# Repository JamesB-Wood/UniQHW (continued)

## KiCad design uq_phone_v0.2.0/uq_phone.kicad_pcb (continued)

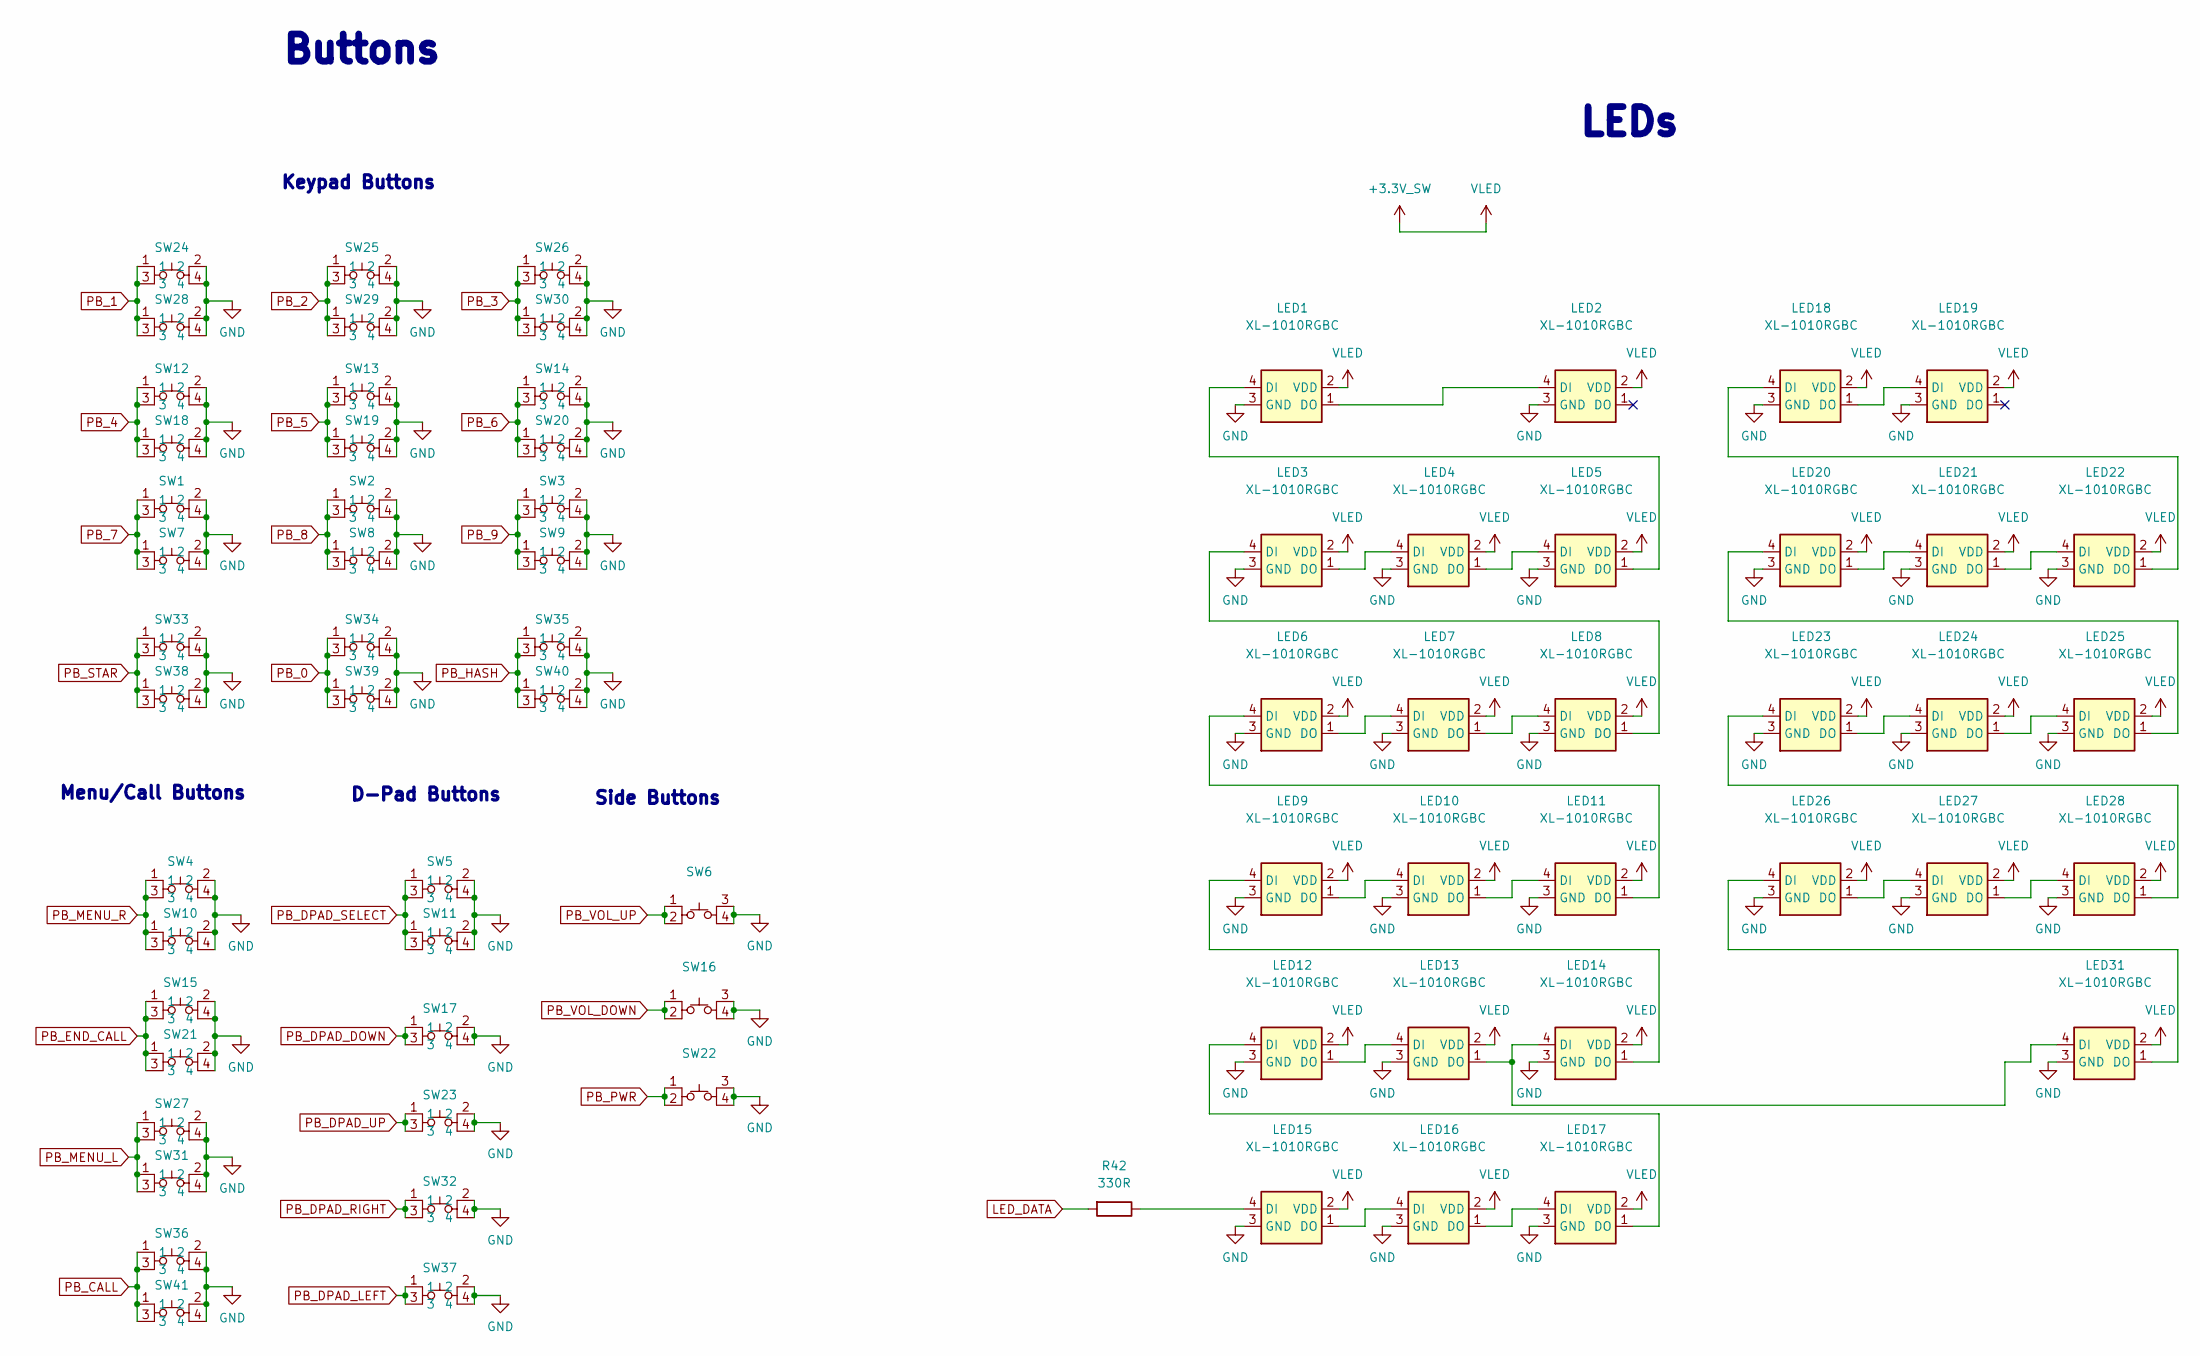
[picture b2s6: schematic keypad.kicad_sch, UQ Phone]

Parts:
LED1, LED2, LED3, LED4, LED5, LED6, LED7, LED8, LED9, LED10, LED11, LED12, LED13, LED14, LED15, LED16, LED17, LED18, LED20, LED21, LED22, LED23, LED24, LED25, LED26, LED27, LED28, LED31: XL-1010RGBC; XL-1010RGBC-WS2812B; LCSC PN C5349953
LED19: XL-1010RGBC; XL-1010RGBC-Alt; LCSC PN C5349953
R42: 330R; R_0402_1005Metric; LCSC PN C6117577
SW1, SW2, SW3, SW4, SW5, SW7, SW8, SW9, SW10, SW11, SW12, SW13, SW14, SW15, SW17, SW18, SW19, SW20, SW21, SW23, SW24, SW25, SW26, SW27, SW28, SW29, SW30, SW31, SW32, SW33, SW34, SW35, SW36, SW37, SW38, SW39, SW40, SW41: SKTAAAE010; LCSC PN C358616
SW6, SW16, SW22: SKSCLCE010; LCSC PN C139799

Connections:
+3.3V_SW: LED1.2 (VDD), LED2.2 (VDD), LED3.2 (VDD), LED4.2 (VDD), LED5.2 (VDD), LED6.2 (VDD), LED7.2 (VDD), LED8.2 (VDD), LED9.2 (VDD), LED10.2 (VDD), LED11.2 (VDD), LED12.2 (VDD), LED13.2 (VDD), LED14.2 (VDD), LED15.2 (VDD), LED16.2 (VDD), LED17.2 (VDD), LED18.2 (VDD), LED19.2 (VDD), LED20.2 (VDD), LED21.2 (VDD), LED22.2 (VDD), LED23.2 (VDD), LED24.2 (VDD), LED25.2 (VDD), LED26.2 (VDD), LED27.2 (VDD), LED28.2 (VDD), LED31.2 (VDD); also elsewhere on the board
GND: LED1.3 (GND), LED2.3 (GND), LED3.3 (GND), LED4.3 (GND), LED5.3 (GND), LED6.3 (GND), LED7.3 (GND), LED8.3 (GND), LED9.3 (GND), LED10.3 (GND), LED11.3 (GND), LED12.3 (GND), LED13.3 (GND), LED14.3 (GND), LED15.3 (GND), LED16.3 (GND), LED17.3 (GND), LED18.3 (GND), LED19.3 (GND), LED20.3 (GND), LED21.3 (GND), LED22.3 (GND), LED23.3 (GND), LED24.3 (GND), LED25.3 (GND), LED26.3 (GND), LED27.3 (GND), LED28.3 (GND), LED31.3 (GND), SW1.2, SW1.4, SW2.2, SW2.4, SW3.2, SW3.4, SW4.2, SW4.4, SW5.2, SW5.4, SW6.3, SW6.4, SW7.2, SW7.4, SW8.2, SW8.4, SW9.2, SW9.4, SW10.2, SW10.4, SW11.2, SW11.4, SW12.2, SW12.4, SW13.2, SW13.4, SW14.2, SW14.4, SW15.2, SW15.4, SW16.3, SW16.4, SW17.2, SW17.4, SW18.2, SW18.4, SW19.2, SW19.4, SW20.2, SW20.4, SW21.2, SW21.4, SW22.3, SW22.4, SW23.2, SW23.4, SW24.2, SW24.4, SW25.2, SW25.4, SW26.2, SW26.4, SW27.2, SW27.4, SW28.2, SW28.4, SW29.2, SW29.4, SW30.2, SW30.4, SW31.2, SW31.4, SW32.2, SW32.4, SW33.2, SW33.4, SW34.2, SW34.4, SW35.2, SW35.4, SW36.2, SW36.4, SW37.2, SW37.4, SW38.2, SW38.4, SW39.2, SW39.4, SW40.2, SW40.4, SW41.2, SW41.4; also elsewhere on the board
LED_DATA: R42.2; also elsewhere on the board
unnamed: LED1.4 (DI), LED5.1 (DO)
unnamed: LED1.1 (DO), LED2.4 (DI)
unnamed: LED3.4 (DI), LED8.1 (DO)
unnamed: LED3.1 (DO), LED4.4 (DI)
unnamed: LED4.1 (DO), LED5.4 (DI)
unnamed: LED6.1 (DO), LED7.4 (DI)
unnamed: LED7.1 (DO), LED8.4 (DI)
unnamed: LED9.1 (DO), LED10.4 (DI)
unnamed: LED10.1 (DO), LED11.4 (DI)
unnamed: LED6.4 (DI), LED11.1 (DO)
unnamed: LED12.4 (DI), LED17.1 (DO)
unnamed: LED12.1 (DO), LED13.4 (DI)
unnamed: LED13.1 (DO), LED14.4 (DI), LED31.4 (DI)
unnamed: LED9.4 (DI), LED14.1 (DO)
unnamed: LED15.4 (DI), R42.1
unnamed: LED15.1 (DO), LED16.4 (DI)
unnamed: LED16.1 (DO), LED17.4 (DI)
unnamed: LED18.4 (DI), LED22.1 (DO)
unnamed: LED18.1 (DO), LED19.4 (DI)
unnamed: LED20.4 (DI), LED25.1 (DO)
unnamed: LED20.1 (DO), LED21.4 (DI)
unnamed: LED21.1 (DO), LED22.4 (DI)
unnamed: LED23.4 (DI), LED28.1 (DO)
unnamed: LED23.1 (DO), LED24.4 (DI)
unnamed: LED24.1 (DO), LED25.4 (DI)
unnamed: LED26.4 (DI), LED31.1 (DO)
unnamed: LED26.1 (DO), LED27.4 (DI)
unnamed: LED27.1 (DO), LED28.4 (DI)
PB_0: SW34.1, SW34.3, SW39.1, SW39.3; also elsewhere on the board
PB_1: SW24.1, SW24.3, SW28.1, SW28.3; also elsewhere on the board
PB_2: SW25.1, SW25.3, SW29.1, SW29.3; also elsewhere on the board
PB_3: SW26.1, SW26.3, SW30.1, SW30.3; also elsewhere on the board
PB_4: SW12.1, SW12.3, SW18.1, SW18.3; also elsewhere on the board
PB_5: SW13.1, SW13.3, SW19.1, SW19.3; also elsewhere on the board
PB_6: SW14.1, SW14.3, SW20.1, SW20.3; also elsewhere on the board
PB_7: SW1.1, SW1.3, SW7.1, SW7.3; also elsewhere on the board
PB_8: SW2.1, SW2.3, SW8.1, SW8.3; also elsewhere on the board
PB_9: SW3.1, SW3.3, SW9.1, SW9.3; also elsewhere on the board
PB_CALL: SW36.1, SW36.3, SW41.1, SW41.3; also elsewhere on the board
PB_DPAD_DOWN: SW17.1, SW17.3; also elsewhere on the board
PB_DPAD_LEFT: SW37.1, SW37.3; also elsewhere on the board
PB_DPAD_RIGHT: SW32.1, SW32.3; also elsewhere on the board
PB_DPAD_SELECT: SW5.1, SW5.3, SW11.1, SW11.3; also elsewhere on the board
PB_DPAD_UP: SW23.1, SW23.3; also elsewhere on the board
PB_END_CALL: SW15.1, SW15.3, SW21.1, SW21.3; also elsewhere on the board
PB_HASH: SW35.1, SW35.3, SW40.1, SW40.3; also elsewhere on the board
PB_MENU_L: SW27.1, SW27.3, SW31.1, SW31.3; also elsewhere on the board
PB_MENU_R: SW4.1, SW4.3, SW10.1, SW10.3; also elsewhere on the board
PB_PWR: SW22.1, SW22.2; also elsewhere on the board
PB_STAR: SW33.1, SW33.3, SW38.1, SW38.3; also elsewhere on the board
PB_VOL_DOWN: SW16.1, SW16.2; also elsewhere on the board
PB_VOL_UP: SW6.1, SW6.2; also elsewhere on the board

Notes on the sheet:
Side Buttons
LEDs
D-Pad Buttons
Keypad Buttons
Menu/Call Buttons
Buttons

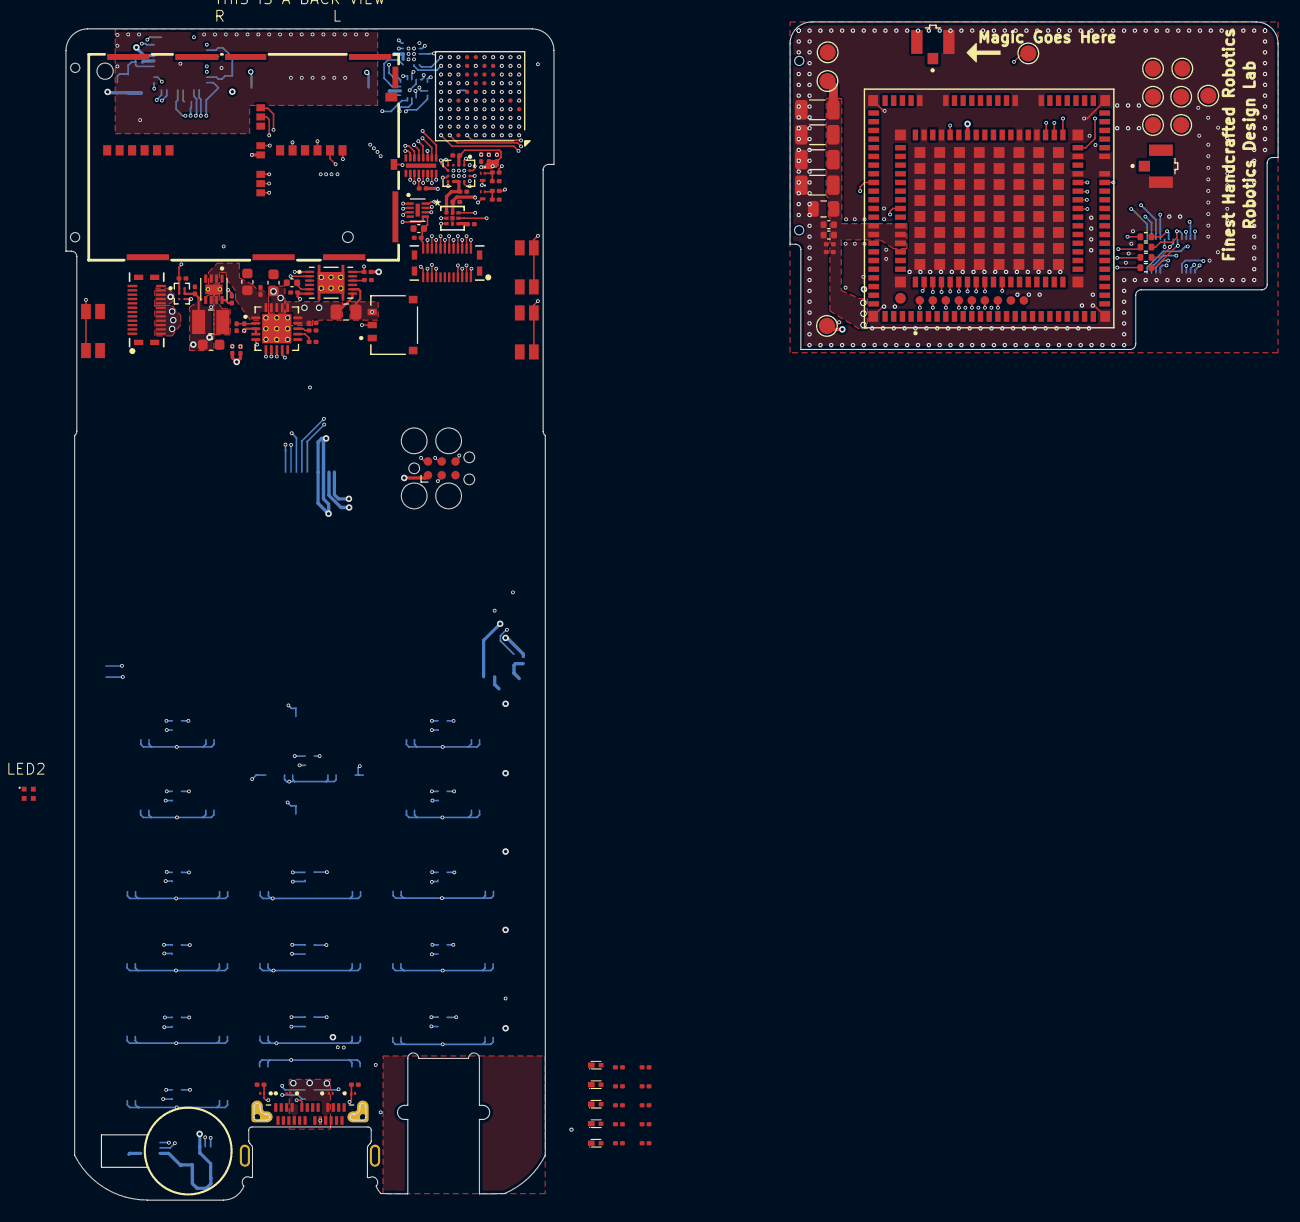
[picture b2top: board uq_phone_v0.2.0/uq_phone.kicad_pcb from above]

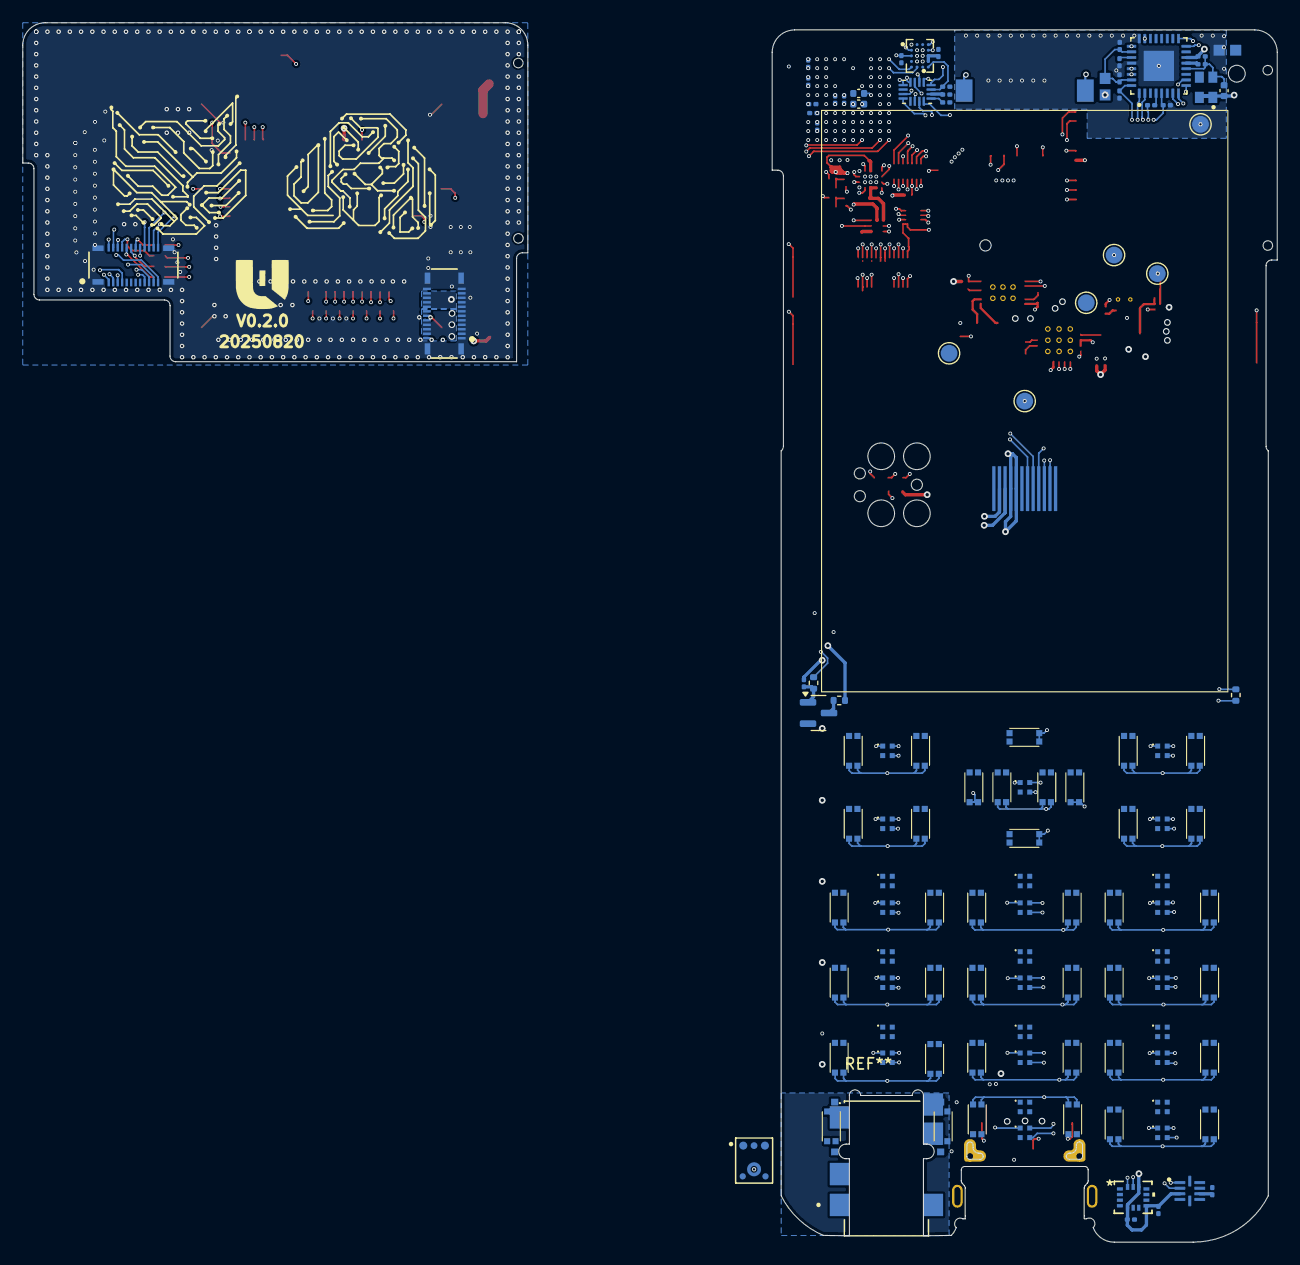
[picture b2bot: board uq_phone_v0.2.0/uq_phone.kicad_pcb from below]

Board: 6 copper layers, 111.8 x 108.6 mm, 220 parts (116 on the bottom side), 198 nets.

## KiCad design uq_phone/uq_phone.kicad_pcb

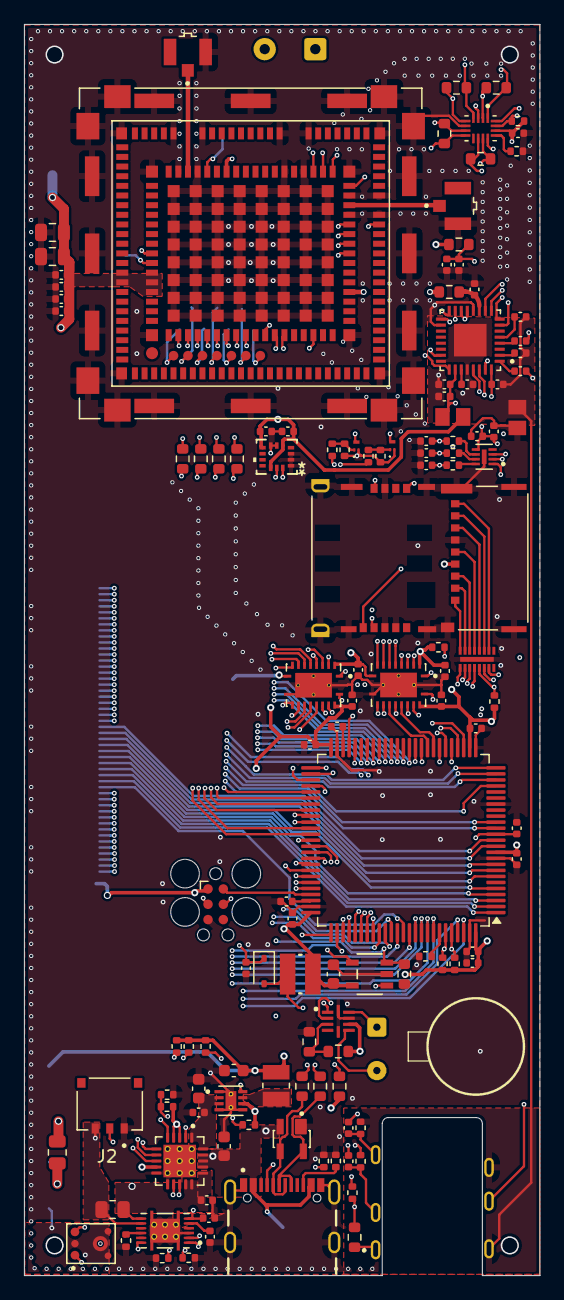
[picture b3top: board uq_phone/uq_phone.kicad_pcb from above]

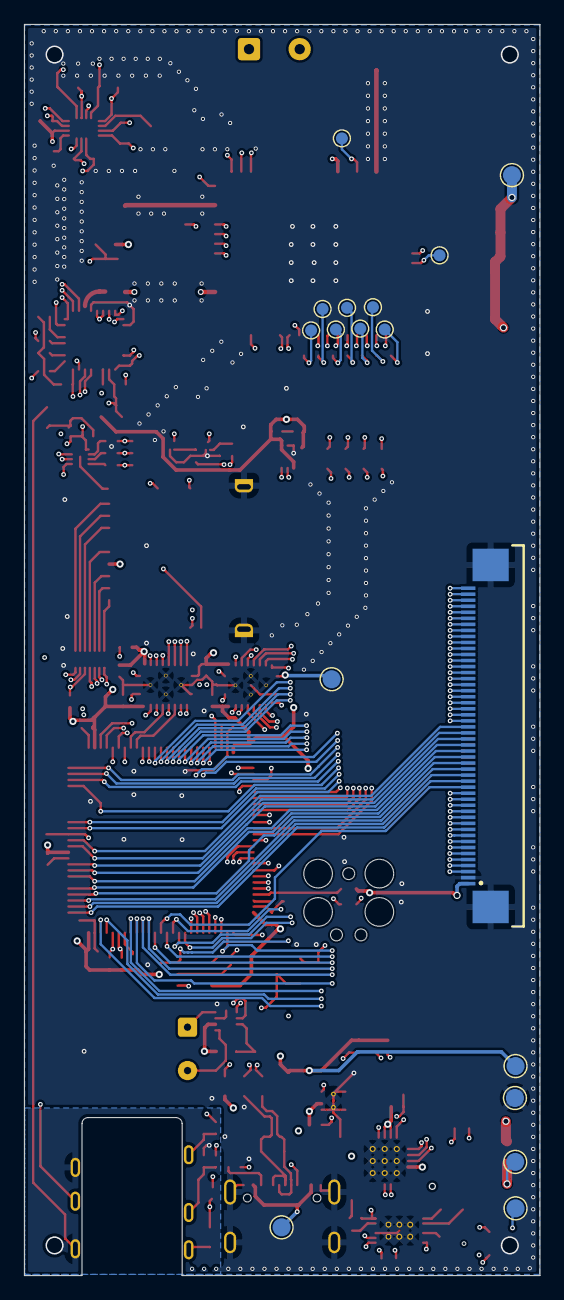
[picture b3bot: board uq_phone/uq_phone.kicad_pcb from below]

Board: 4 copper layers, 42.8 x 103.8 mm, 146 parts (17 on the bottom side), 194 nets.

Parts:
C1, C4, C34: 10uF; C_0603_1608Metric
C2, C3, C19, C35, C42, C44, C45, C46, C47, C48, C49: 4.7uF; C_0402_1005Metric
C5: 470pF; C_0402_1005Metric
C6, C11, C37, C38, C39, C41, C43: 1uF; C_0402_1005Metric
C7: 22uF; C_0603_1608Metric
C8: 10pF; C_0402_1005Metric
C9: 10nF; C_0402_1005Metric
C10, C14, C15, C16, C17, C18, C22, C23, C24, C25, C26, C27, C28, C32, C36: 100nF; C_0402_1005Metric
C12, C13: 47uF; C_0805_2012Metric
C20, C21: 2.2uF; C_0402_1005Metric
C29, C30, C31: 22pF; C_0402_1005Metric
C33, C40: 33pF; C_0402_1005Metric
D1: SP0503BAHTG; SOT143
D2: PMEG2010EA; D_SOD-323
FB1, FB2: MPZ2012S221AT000; BEADC2012X105N
J1: USB4105-GF-A; GCT_USB4105-GF-A
J2: BM03B-ACHSS-GAN-TF_LF__SN_; JST_BM03B-ACHSS-GAN-TF_LF__SN_
J3, J4: 20279-001E-03; IPEX_20279-001E-03
J5: 6871XX14022_68715014022; 68715014022
J6: Conn_ARM_SWD_TagConnect_TC2030; Tag-Connect_TC2030-IDC-FP_2x03_P1.27mm_Vertical
J7: Conn_01x02; SolderWire-0.1sqmm_1x02_P3.6mm_D0.4mm_OD1mm
J8: KP15B-6S-SF_800_; HIROSE_KP15B-6S-SF_800_
J10: SJ-3551B-MSMT-TR-67; CUI_SJ-3551B-MSMT-TR-67
J11: Conn_01x02; SolderWire-0.25sqmm_1x02_P4.2mm_D0.65mm_OD1.7mm
L1: 3.3uH; INDC2520X120N
L2: 4.7uH; WE-MAPI_3015
M1: VCDM0834B004L; Motor_8mm
MK1: AMM-3738-B-R; MIC_AMM-3738-B-R
Q1, Q2: MMBT3904LP-7; DFN101X61X53-3N
R1: 270k; R_0402_1005Metric
R2, R4, R11: 100k; R_0402_1005Metric
R3, R38: 2.2k; R_0402_1005Metric
R5, R6, R9: 5.1k; R_0402_1005Metric
R7, R26, R27, R33, R35, R36, R39, R44, R49: 10k; R_0402_1005Metric
R8: 10m; R_0805_2012Metric
R10: 0R; R_0805_2012Metric
R12, R17, R24, R25: 4.7k; R_0402_1005Metric
R13, R18, R45: 47k; R_0402_1005Metric
R14, R15, R16, R19, R20, R21, R22, R28, R29, R37, R40, R41, R42, R43, R46, R47: 0R; R_0603_1608Metric
R30, R31, R32: 22R; R_0402_1005Metric
R34: 3.83R; R_0603_1608Metric
TP1, TP2, TP3, TP4, TP5, TP6, TP7: TestPoint; TestPoint_Pad_D1.5mm
TP8, TP9, TP10, TP11, TP12, TP13, TP14, TP15, TP16: TestPoint; TestPoint_Pad_D1.0mm
U1: MCP73871-2CCI_ML; QFN50P400X400X100-21N
U2: TPS62162DSGR; SON50P200X200X80-9N
U3: BQ27441DRZR-G1A; IC_BQ27441DRZR-G1A
U4: WP SNAP-IN BASE_6000636; SIERRA_WP_SNAP-IN_BASE
U5, U6: TXB0108RGYR; IC_TXB0108RGYR
U7: STM32H733VGTx; LQFP-100_14x14mm_P0.5mm
U8: LSM6DSVTR; LGA14-L_2P59X3P1X0P5_STM
U9: DRV2603RUNR; QFN50P200X200X80-10N
U10: TPD3F303DQDR; SON40P170X135X80-9N
U11: TPD8F003DQDR; SON40P135X330X80-17N
U12: MCP1664T-E/OT; SOT-23-5_OT_MCH
U13: TS3A5018RSVR; QFN40P260X180X55-16N
U14: NAU88C22YG; QFN50P500X500X80-33N

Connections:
+1.8V: C14.1, C15.1, C36.1, R35.2, R45.2, R47.1, TP7.1, U4.45 (VGPIO), U5.2 (VCCA), U5.10 (OE), U6.2 (VCCA), U6.10 (OE), U13.14 (V+)
+3.3V: C7.1, C16.1, C17.1, C19.1, C22.2, C23.2, C24.2, C25.2, C26.2, C27.1, C28.1, C34.1, FB2.2, J5.1, J6.1 (VCC), J8.C4_1 (VDD), L1.2, L2.1, R9.2, R11.2, R24.2, R25.2, R26.2, R27.2, R28.2, R33.2, TP3.1, U2.6 (VOS), U5.19 (VCCB), U6.19 (VCCB), U7.11 (VDD), U7.27 (VDD), U7.50 (VDD), U7.75 (VDD), U7.100 (VDD), U8.5 (VDD_IO), U8.8 (VDD), U8.12 (CS), U9.7 (VDD), U12.5 (VIN)
+VMOB: C8.1, C9.1, C10.1, C11.1, C12.1, C13.1, R10.1, TP6.1, U4.61 (VBAT_RF), U4.62 (VBAT_RF__1), U4.63 (VBAT_BB), U4.157 (VBAT_RF__2), U4.158 (VBAT_BB__1)
/Mobile/MOB_USB_N: R14.1, U4.12 (USB_D-)
/Mobile/MOB_USB_P: R15.1, U4.13 (USB_D+)
AGND: C41.2, C43.1, C45.2, C47.2, C48.2, C49.2, FB1.2, J10.4, J10.6, MK1.2 (GND), MK1.3 (GND__1), MK1.5 (GND__2), MK1.6_1 (GND__3), MK1.6_2 (GND__4), R39.2, R44.2, TP4.1, U14.24 (VSSSPK), U14.28 (VSSA), U14.33 (EXP)
AUD_BCLK: R41.2, U13.5 (COM2), U14.8 (BCLK)
AUD_IN: R42.2, U13.7 (COM3), U14.9 (ADCOUT)
AUD_OUT: R43.2, U13.10 (COM4), U14.10 (DACIN)
AUD_SCL: U6.3 (A2), U14.16 (SCLK)
AUD_SDA: U6.1 (A1), U14.17 (SDIO)
AUD_SW_H: U6.14 (B6), U7.34 (PB0)
AUD_SW_L: R35.1, U6.7 (A6), U13.15 (IN)
AUD_SYNC: R40.2, U13.2 (COM1), U14.7 (FS)
BAT_THERM: J2.2, U1.5 (THERM)
DISP_BL: U7.46 (PB10), U12.4 (EN)
DISP_CS: J5.17, U7.88 (PD7)
DISP_DB0: J5.29, U7.61 (PD14)
DISP_DB1: J5.28, U7.62 (PD15)
DISP_DB2: J5.40, U7.81 (PD0)
DISP_DB3: J5.41, U7.82 (PD1)
DISP_DB4: J5.50, U7.37 (PE7)
DISP_DB5: J5.49, U7.38 (PE8)
DISP_DB6: J5.48, U7.39 (PE9)
DISP_DB7: J5.47, U7.40 (PE10)
DISP_DB8: J5.46, U7.41 (PE11)
DISP_DB9: J5.45, U7.42 (PE12)
DISP_DB10: J5.44, U7.43 (PE13)
DISP_DB11: J5.43, U7.44 (PE14)
DISP_DB12: J5.42, U7.45 (PE15)
DISP_DB13: J5.33, U7.55 (PD8)
DISP_DB14: J5.32, U7.56 (PD9)
DISP_DB15: J5.31, U7.57 (PD10)
DISP_DC: J5.30, U7.58 (PD11)
DISP_LEDA: C35.1, D2.1 (K), J5.12
DISP_LEDK: J5.13, R34.2, U12.3 (VFB)
DISP_RD: J5.15, U7.85 (PD4)
DISP_RES: J5.14, U7.84 (PD3)
DISP_WR: J5.16, U7.86 (PD5)
FUEL_GPO: R9.1, U3.12 (GPOUT), U7.51 (PB12)
GND: C1.2, C2.2, C3.2, C4.1, C5.2, C6.2, C7.2, C8.2, C9.2, C10.2, C11.2, C12.2, C13.2, C14.2, C15.2, C16.2, C17.2, C18.1, C19.2, C20.2, C21.2, C22.1, C23.1, C24.1, C25.1, C26.1, C27.2, C28.2, C29.2, C30.2, C31.2, C32.2, C33.2, C34.2, C35.2, C36.2, C40.2, C44.2, C46.2, D1.1, FB1.1, J1.A1_B12 (GND), J1.B1_A12 (GND), J1.SH1 (SHELL_GND), J1.SH2 (SHELL_GND), J1.SH3 (SHELL_GND), J1.SH4 (SHELL_GND), J2.1, J3.2, J4.2, J5.2, J5.Z1, J5.Z2, J6.5 (GND), J8.C5_2 (GND), J8.C6_1 (VSS), J8.G1 (GND__1), J8.G2 (GND__2), J8.S1 (SHIELD), J8.S2 (SHIELD__1), J8.S3 (SHIELD__2), J8.S4 (SHIELD__3), J8.S5 (SHIELD__4), J8.S6 (SHIELD__5), J8.S7 (SHIELD__6), J8.S8 (SHIELD__7), J8.S9 (SHIELD__8), J8.S10 (SHIELD__9), Q1.2, Q2.2, R2.1, R3.2, R4.1, R5.1, R6.1, R7.1, R13.1, R18.1, R29.1, R34.1, R36.1, R49.1, TP2.1, U1.10 (VSS__1), U1.11 (VSS), U1.21 (EP), U2.1 (PGND), U2.4 (AGND), U2.5 (FB), U2.9 (EXP), U3.3 (VSS), U3.13 (EXP), U4.30 (GND_1), U4.32 (GND_1__1), U4.37 (GND_1__2), U4.39 (GND_1__3), U4.48 (GND_1__4), U4.50 (GND_1__5), U4.67 (GND_1__6), U4.68 (GND_1__7), U4.69 (GND_1__8), U4.70 (GND_1__9), U4.111 (GND_1__10), U4.113 (GND_1__11), U4.125 (GND_1__12), U4.128 (GND_1__13), U4.136 (GND_1__14), U4.139 (GND_2), U4.167 (GND_2__1), U4.168 (GND_2__2), U4.169 (GND_2__3), U4.170 (GND_2__4), U4.171 (GND_2__5), U4.172 (GND_2__6), U4.173 (GND_2__7), U4.174 (GND_2__8), U4.175 (GND_2__9), U4.176 (GND_2__10), U4.177 (GND_2__11), U4.178 (GND_2__12), U4.179 (GND_2__13), U4.180 (GND_2__14), U4.181 (GND_3), U4.182 (GND_3__1), U4.183 (GND_3__2), U4.184 (GND_3__3), U4.185 (GND_3__4), U4.186 (GND_3__5), U4.187 (GND_3__6), U4.188 (GND_3__7), U4.189 (GND_3__8), U4.190 (GND_3__9), U4.191 (GND_3__10), U4.192 (GND_3__11), U4.193 (GND_3__12), U4.194 (GND_3__13), U4.195 (GND_4), U4.196 (GND_4__1), U4.197 (GND_4__2), U4.198 (GND_4__3), U4.199 (GND_4__4), U4.200 (GND_4__5), U4.201 (GND_4__6), U4.202 (GND_4__7), U4.203 (GND_4__8), U4.204 (GND_4__9), U4.205 (GND_4__10), U4.206 (GND_4__11), U4.207 (GND_4__12), U4.208 (GND_4__13), U4.209 (GND_4__14), U4.210 (GND_5), U4.211 (GND_5__1), U4.212 (GND_5__2), U4.213 (GND_5__3), U4.214 (GND_5__4), U4.215 (GND_5__5), U4.216 (GND_5__6), U4.217 (GND_5__7), U4.218 (GND_5__8), U4.219 (GND_5__9), U4.220 (GND_5__10), U4.221 (GND_5__11), U4.222 (GND_5__12), U4.223 (GND_5__13), U4.224 (GND_5__14), U4.225 (GND_6), U4.226 (GND_6__1), U4.227 (GND_6__2), U4.228 (GND_6__3), U4.229 (GND_6__4), U4.230 (GND_6__5), U4.231 (GND_6__6), U4.232 (GND_6__7), U4.233 (GND_6__8), U4.234 (GND_6__9), U4.P1, U4.P2, U4.P3, U4.P4, U4.P5, U4.P6, U4.P7, U4.P8, U4.P9, U4.P10, U4.P11, U4.P12, U4.P13, U4.P14, U4.P15, U4.P16, U4.P17, U4.P18, U4.P19, U4.P20, U5.11 (GND), U5.21 (EXP), U5.21_1 (EXP__1), U5.21_2 (EXP__2), U5.21_3 (EXP__3), U5.21_4 (EXP__4), U6.11 (GND), U6.21 (EXP), U6.21_1 (EXP__1), U6.21_2 (EXP__2), U6.21_3 (EXP__3), U6.21_4 (EXP__4), U7.10 (VSS), U7.19 (VSSA), U7.26 (VSS), U7.49 (VSS), U7.74 (VSS), U7.99 (VSS), U8.1 (SDO/SA0), U8.2 (SDX), U8.3 (SCX), U8.6 (GND), U8.7 (GND), U9.5 (GND), U9.8 (GND__1), U9.10 (GND__2), U10.9 (GND), U11.17 (GND), U12.2 (GND), U13.6 (GND), U14.12 (VSSD), U14.18 (MODE)
HP_DET: J10.5, R45.1, U6.5 (A4), U14.15 (CSB/GPIO1)
HP_DET_MCU: U6.16 (B4), U7.33 (PC5)
HP_LEFT: C38.1, U14.30 (LHP)
HP_MIC: C37.1, U14.4 (RMICP)
HP_RIGHT: C39.1, U14.29 (RHP)
LED_DATA: J5.39, U7.25 (PA3)
MCP_OUT: C3.1, C4.2, U1.1 (OUT), U1.20 (OUT__1), U2.2 (VIN), U2.3 (EN)
MCP_PG: U1.6 (~PG), U7.52 (PB13)
MCP_STAT1: R27.1, U1.8 (STAT1/*LBO), U7.54 (PB15)
MCP_STAT2: R26.1, U1.7 (STAT2), U7.53 (PB14)
MCU_AUD_BCLK_H: U6.13 (B7), U7.29 (PA5)
MCU_AUD_BCLK_L: U6.8 (A7), U13.3 (NC2)
MCU_AUD_OUT_L: U6.9 (A8), U13.12 (NC4)
MCU_AUD_OUT_L_H: U6.12 (B8), U7.31 (PA7)
MCU_AUD_SYNC_H: U6.15 (B5), U7.28 (PA4)
MCU_AUD_SYNC_L: U6.6 (A5), U13.16 (NC1)
MCU_CTS: U5.14 (B6), U7.70 (PA11)
MCU_DCD: U5.18 (B2), U7.59 (PD12)
MCU_DSR: U5.20 (B1), U7.67 (PA8)
MCU_DTR: U5.17 (B3), U7.60 (PD13)
MCU_RI: U5.12 (B8), U7.63 (PC6)
MCU_RTS: U5.13 (B7), U7.71 (PA12)
MCU_RXD: U5.16 (B4), U7.69 (PA10)
MCU_TXD: U5.15 (B5), U7.68 (PA9)
MIC_BIAS: C45.1, MK1.4 (VDD), R38.2, U14.32 (MICBIAS)
MIC_GND: C43.2, U14.2 (LMICN)
MIC_OUT: C42.2, U14.1 (LMICP)
MOB_AUD_BCLK: R41.1, U4.36 (PCM_CLK/I2S_CLK), U13.4 (NO2)
MOB_AUD_IN: R42.1, U4.34 (PCM_IN/I2S_IN), U13.8 (NO3)
MOB_AUD_OUT: R43.1, U4.33 (PCM_OUT/I2S_OUT), U13.11 (NO4)
MOB_AUD_SYNC: R40.1, U4.35 (PCM_SYNC/I2S_WS), U13.1 (NO1)
MOB_AUX_ANT: J4.1 (Contact), U4.31 (RF_DIV)
MOB_CTS: R22.2, U5.7 (A6)
MOB_DCD: U4.8 (UART1_DCD), U5.3 (A2)
MOB_DSR: U4.9 (UART1_DSR), U5.1 (A1)
MOB_DTR: U4.7 (UART1_DTR), U5.4 (A3)
MOB_MAIN_ANT: J3.1 (Contact), U4.49 (RF_MAIN)
MOB_PWR: Q1.3, U4.59 (~POWER_ON)
MOB_PWR_CTL: R12.2, U7.36 (PB2)
MOB_RI: U4.2 (UART1_RI), U5.9 (A8)
MOB_RST: Q2.3, U4.11 (~RESET_IN)
MOB_RST_CTL: R17.2, U7.47 (PB11)
MOB_RTS: R20.2, U5.8 (A7)
MOB_RXD: R21.2, U5.5 (A4)
MOB_SYS_CLK: R46.2, U4.22 (SYS_CLK)
MOB_TXD: R19.2, U5.6 (A5)
MOB_WAKE_H: U6.17 (B3), U7.35 (PB1)
MOB_WAKE_L: U4.110 (WAKE_ON_WWAN), U6.4 (A3)
unnamed: C20.1, U7.48 (VCAP)
unnamed: C21.1, U7.73 (VCAP)
unnamed: C37.2, R37.1, R38.1
unnamed: C38.2, J10.2, R39.1
unnamed: C39.2, J10.3, R44.1
unnamed: D2.2 (A), L2.2, U12.1 (SW)
unnamed: J1.A5 (CC1), R6.2
unnamed: J1.B5 (CC2), R5.2
unnamed: J7.1, U9.9 (OUT_P)
unnamed: J7.2, U9.6 (OUT_M)
unnamed: J8.C2_1 (CD/DATA3), U11.15 (CH2_OUT)
unnamed: J8.C5_1 (CLK), U11.13 (CH4_OUT)
unnamed: J8.C3_1 (CMD), U11.14 (CH3_OUT)
unnamed: J8.C7_1 (DAT0), U11.11 (CH6_OUT)
unnamed: J8.C8_1 (DAT1), U11.10 (CH7_OUT)
unnamed: J8.C1_1 (DAT2), U11.16 (CH1_OUT)
unnamed: J8.C3_2 (CLK_2), U10.2 (CLK_OUT)
unnamed: J8.C7_2 (I/O), U10.3 (DATA2_OUT)
unnamed: J8.C2_2 (RST), U10.1 (DATA1_OUT)
unnamed: J10.1, R37.2
unnamed: C42.1, MK1.1 (OUTPUT)
unnamed: Q1.1, R12.1, R13.2
unnamed: Q2.1, R17.1, R18.2
unnamed: R3.1, U1.13 (PROG1)
unnamed: R4.2, U1.12 (PROG3)
unnamed: R1.1, R2.2, U1.2 (VPCC)
unnamed: R11.1, U2.8 (PG)
unnamed: L1.1, U2.7 (SW)
unnamed: C6.1, J2.3, R8.1, U3.6 (BAT), U3.8 (SRP)
unnamed: R7.2, U3.10 (BIN)
unnamed: C5.1, U3.5 (VDD)
unnamed: TP10.1, U4.236 (J1)
unnamed: TP11.1, U4.237 (J2)
unnamed: TP12.1, U4.238 (J3)
unnamed: TP13.1, U4.239 (J4)
unnamed: TP14.1, U4.240 (J5)
unnamed: TP15.1, U4.241 (J6)
unnamed: TP16.1, U4.242 (J7)
unnamed: TP8.1, U4.47 (TP1_BOOTPIN)
unnamed: TP9.1, U4.60 (TX_ON)
unnamed: R22.1, U4.4 (UART1_CTS)
unnamed: R20.1, U4.3 (UART1_RTS)
unnamed: R21.1, U4.6 (UART1_RX)
unnamed: R19.1, U4.5 (UART1_TX)
unnamed: R16.1, U4.16 (USB_VBUS)
unnamed: R49.2, U7.94 (BOOT0)
unnamed: R28.1, R29.2, U9.3 (LRA/~ERM)
unnamed: R32.1, U10.7 (CLK_IN)
unnamed: R31.1, U10.8 (DATA1_IN)
unnamed: R30.1, U10.6 (DATA2_IN)
unnamed: J8.D_T_1, U11.12 (CH5_OUT)
unnamed: R36.2, U13.13 (~EN)
unnamed: C40.1, R46.1, U14.11 (MCLK)
unnamed: C41.1, U14.5 (RMICN)
unnamed: C47.1, C49.1, FB2.1, U14.26 (VDDSPK), U14.31 (VDDA)
unnamed: C44.1, C46.1, R47.2, U14.13 (VDDC), U14.14 (VDDB)
unnamed: C48.1, U14.27 (VREF)
PB_0: J5.3, U7.98 (PE1)
PB_1: J5.19, U7.2 (PE3)
PB_2: J5.20, U7.3 (PE4)
PB_3: J5.21, U7.4 (PE5)
PB_4: J5.22, U7.5 (PE6)
PB_5: J5.23, U7.7 (PC13)
PB_6: J5.24, U7.8 (PC14)
PB_7: J5.25, U7.9 (PC15)
PB_8: J5.26, U7.12 (PH0)
PB_9: J5.27, U7.13 (PH1)
PB_CALL: J5.10, U7.87 (PD6)
PB_DPAD_DOWN: J5.8, U7.90 (PB4(NJTRST))
PB_DPAD_LEFT: J5.6, U7.92 (PB6)
PB_DPAD_RIGHT: J5.7, U7.91 (PB5)
PB_DPAD_SELECT: J5.5, U7.93 (PB7)
PB_DPAD_UP: J5.9, U7.89 (PB3(JTDO)
PB_END_CALL: J5.11, U7.77 (PA15(JTDI))
PB_HASH: J5.18, U7.1 (PE2)
PB_MENU_L: J5.34, U7.15 (PC0)
PB_MENU_R: J5.35, U7.16 (PC1)
PB_PWR: J5.36, U7.22 (PA0)
PB_STAR: J5.4, U7.97 (PE0)
PB_VOL_DOWN: J5.37, U7.23 (PA1)
PB_VOL_UP: J5.38, U7.24 (PA2)
RST: C18.2, J6.3 (~RESET), U7.14 (NRST)
SCL: R24.1, U3.2 (SCL), U6.18 (B2), U7.95 (PB8), U8.13 (SCL)
SDA: R25.1, U3.1 (SDA), U6.20 (B1), U7.96 (PB9), U8.14 (SDA)
SIM_CLK: C29.1, R32.2, U4.28 (UIM1_DATA)
SIM_DATA: C31.1, R30.2, U4.27 (UIM1_CLK)
SIM_RST: C30.1, R31.2, U4.29 (~UIM1_RESET)
SIM_VDD: C32.1, C33.1, J8.C1_2 (VCC), U4.26 (UIM1_VCC), U10.5 (VCC)
SPEAKER_N: J11.2, U14.25 (LSPKOUT)
SPEAKER_P: J11.1, U14.23 (RSPKOUT)
SWCLK: J6.4 (SWCLK), U7.76 (PA14(JTCK)
SWDIO: J6.2 (SWDIO), U7.72 (PA13(JTMS)
USB_N: D1.3, J1.A7 (DN1), J1.B7 (DN2), R14.2
USB_P: D1.4, J1.A6 (DP1), J1.B6 (DP2), R15.2
VBAT: C2.1, R8.2, R10.2, TP5.1, U1.14 (VBAT__1), U1.15 (VBAT), U1.16 (VBAT_SENSE), U3.7 (SRN)
VIB_EN: U7.32 (PC4), U9.1 (EN)
VIB_PWM: U7.30 (PA6), U9.2 (PWM)
VUSB: C1.1, D1.2, J1.A4_B9 (VBUS), J1.B4_A9 (VBUS), R1.2, R16.2, TP1.1, U1.3 (SEL), U1.4 (PROG2), U1.9 (~TE), U1.17 (CE), U1.18 (IN), U1.19 (IN__1)
uSD_CLK: U7.80 (PC12), U11.4 (CH4_IN)
uSD_CMD: U7.83 (PD2), U11.3 (CH3_IN)
uSD_DAT0: U7.65 (PC8), U11.6 (CH6_IN)
uSD_DAT1: U7.66 (PC9), U11.7 (CH7_IN)
uSD_DAT2: U7.78 (PC10), U11.1 (CH1_IN)
uSD_DAT3: U7.79 (PC11), U11.2 (CH2_IN)
uSD_DET: R33.1, U7.64 (PC7), U11.5 (CH5_IN)
